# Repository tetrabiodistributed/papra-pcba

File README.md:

# PAPRA Printed Circuit Board Assembly (PCBA)

PAPRa PCBA - printed circuit board assembly for the PAPRa M12 Controller

Full documentation page for building the PAPRa can be found here: https://tetrabiodistributed.github.io/papra/

Firmware for flashing the PAPRA PCBA can be found here: https://github.com/tetrabiodistributed/papra-pcb-firmware/tree/main/papracode

## PAPRa PCBA comes in 2 form factors

### Thru Hole Technology

* Part Number A-TET-001113
* Suitable for hand soldering
* Larger form factor
* Easy to assemble, intended for novice 
* BOM parts should be easy to source
* Uses Adafruit QT PY or Seeed Xiao microcontroller board
* Firmware: TBD

### SMT

* Part Number A-TET-001100
* Suitable for mass production
* Smallest form factor
* Machine assembly recommended, very difficult to hand solder
* Lowest BOM cost
* Uses ATTINY 0/1/2-Series 14pin SOIC
* Firmware found here: https://github.com/tetrabiodistributed/papra-pcb-firmware/tree/main/papracode

## Notes for programming

* Make a UPDI Programmer: https://create.arduino.cc/projecthub/john-bradnam/create-your-own-updi-programmer-1e55f1?ref=user&ref_id=466812&offset=6
* The board features a UPDI header on the top left of the PCB (top being the side with the battery connectors) the pins are top to bottom 5V, GND and data. 
* Setup Arduino: https://www.hackster.io/john-bradnam/using-the-new-attiny-processors-with-arduino-ide-612185
* You will need to use the megaTinyCore library by SpenceKonde: https://github.com/SpenceKonde/megaTinyCore

Upload settings can be found in the arduino program. 

Please note that there are a number of ATTiny SKUs that are compatible with this PCB and code, please refer to the below table when choosing an appropriate IC.

| Model number   | Confirmed   | Notes                             |
| -------------- | ----------- | --------------------------------- |
| ATtiny204SSN_, | Yes         | See Below(1)  |
| ATtiny404SSN_, | Yes         |    	                           |
| ATtiny804SSN_, | Yes         |                                   |
| ATtiny1604SSN_,| Yes         |    	                           |
| ATtiny214SSN_, | Yes         | See Below(1)  |
| ATtiny414SSN_, | Yes         |    	                           |
| ATtiny814SSN_, | Yes         |                                   |
| ATtiny1614SSN_,| Yes         |    	                           |
| ATtiny1624SSU, | Yes         |    	                           |

(1)ATtiny 204 and 214 have limited (2K) flash memory for program space, but the firmware can be made to fit by sacraficing the bootup LED sequence.

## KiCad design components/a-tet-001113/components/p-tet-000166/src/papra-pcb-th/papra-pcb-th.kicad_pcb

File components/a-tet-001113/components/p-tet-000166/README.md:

# P-TET-000166 — PAPRa M12 Controller PCB (through-hole)

## Files

| Path | What |
|---|---|
| `src/Papra TH_eagle.sch`, `src/Papra TH_eagle.brd` | Original Eagle 9.6.2 design. Source of truth for the migration. |
| `src/papra-pcb-th/` | KiCad 10 project **generated** from the Eagle files by `make import`. Do not hand-edit until the Eagle files are retired; regenerate instead. |
| `src/papra-pcb-th/papra-pcb-th.pretty/`, `papra-pcb-th.kicad_sym` | Project footprint/symbol libraries extracted from the Eagle design. |
| `src/papra-pcb-th/3d/` | Manufacturer STEP models (see `3d/SOURCES.md`). |
| `dist/Papra TH_eagle_2023-03-08.zip` | Gerbers Eagle produced for the fab run. The Gerber check compares against these. |
| `../../lcsc-parts.csv` | LCSC numbers looked up for the BOM MPNs (`make lcsc`). |

## How the migration is validated (`make check`, from the repo root)

1. **Board structure** (`checks/test_board.py`): every Eagle element is a KiCad footprint with the
   same value, position, side; every pad has the same position, drill and copper size; every
   net has the same pads; the GND pour survived.
2. **Schematic** (`checks/test_schematic.py`): KiCad's own netlister reproduces Eagle's nets pad
   for pad; ERC has no errors; KiCad's schematic-parity DRC agrees board with schematic; the
   board passes the design rules translated from Eagle's `.brd`.
3. **Fab output** (`checks/test_gerbers.py`): Gerbers plotted from the KiCad board are rendered
   and XOR-compared per layer against the 2023 Eagle Gerbers; the drill files must list
   identical holes. Overlays land in `build/p-tet-000166/render/diff-<layer>.png`.
4. **3D placement** (`checks/test_models.py`): every model is placed with KiCad's own model
   transform (`checks/model_geom.py`, the matrix chain from the 3D viewer, on the geometry
   KiCad loads from the STEP file) and must sit on its side of the board with only its pins
   through it, landing on its pads. Manufacturer parts are held to datasheet numbers in
   `checks/parts.py` `PLACEMENT` (height, pin length, footprint, which way it faces).
5. **Determinism** (`checks/test_project.py`): a re-import of unchanged sources gives
   byte-identical files. kicad-cli and pcbnew mint random UUIDs and write elements in memory
   order; `checks/stable_ids.py` renames UUIDs by ordinal and sorts the board's blocks.

Known, accepted differences are listed in `checks/config.py` and `checks/project.py`.

## Regenerating

```
make import     # Eagle -> KiCad (board via kicad-cli, schematic via checks/sch_convert.py)
make check
make outputs    # ERC/DRC reports, PDFs, BOMs, Gerbers, drills, STEP, renders in build/
```

## Working in the KiCad GUI

- Open `src/papra-pcb-th/papra-pcb-th.kicad_pro`, not the `.kicad_sch` or `.kicad_pcb` on
  their own. The project carries the symbol/footprint library tables and the DRC/ERC
  severities; opened standalone, KiCad reports every library as missing and uses its
  default rules.
- Close KiCad before `make import`. KiCad keeps the project settings in memory and writes
  them back on save, which silently reverts the generated `.kicad_pro`.

## Additions over the Eagle design

- **Plated slots for the DC jack.** Eagle emulated the PJ-066A blade slots with pads, end
  holes and milling; the KiCad board has one plated oval pad per blade (`checks/parts.py`
  `SLOT_PADS`), which is what the fab produces and what DRC can reason about.
- **QR code on the bottom silkscreen** linking to https://tetrab.io, generated by
  `checks/qr.py` (content and module size in `checks/parts.py`) and placed automatically in
  the largest area free of holes, pads and other silkscreen. It is excluded from the Gerber
  comparison against the 2023 Eagle output, as are the slot pads.
- **3D models.** Standard parts use the models shipped with KiCad. The FASTON tabs, BNC,
  potentiometer and XIAO use manufacturer STEP files under `src/papra-pcb-th/3d/`
  (`3d/SOURCES.md`); their rotation and offset were solved, not eyeballed, by
  `checks/model_solve.py` from the model geometry and the datasheet rules, and are pinned in
  `checks/models.py`. The DC jack is drawn with KiCad's PJ-063AH model because Same Sky
  publishes none for the PJ-066A. To re-solve after changing a model or a rule:

  ```
  .venv/bin/python -m checks.model_solve POT1 H2 BATT+0 U1
  ```

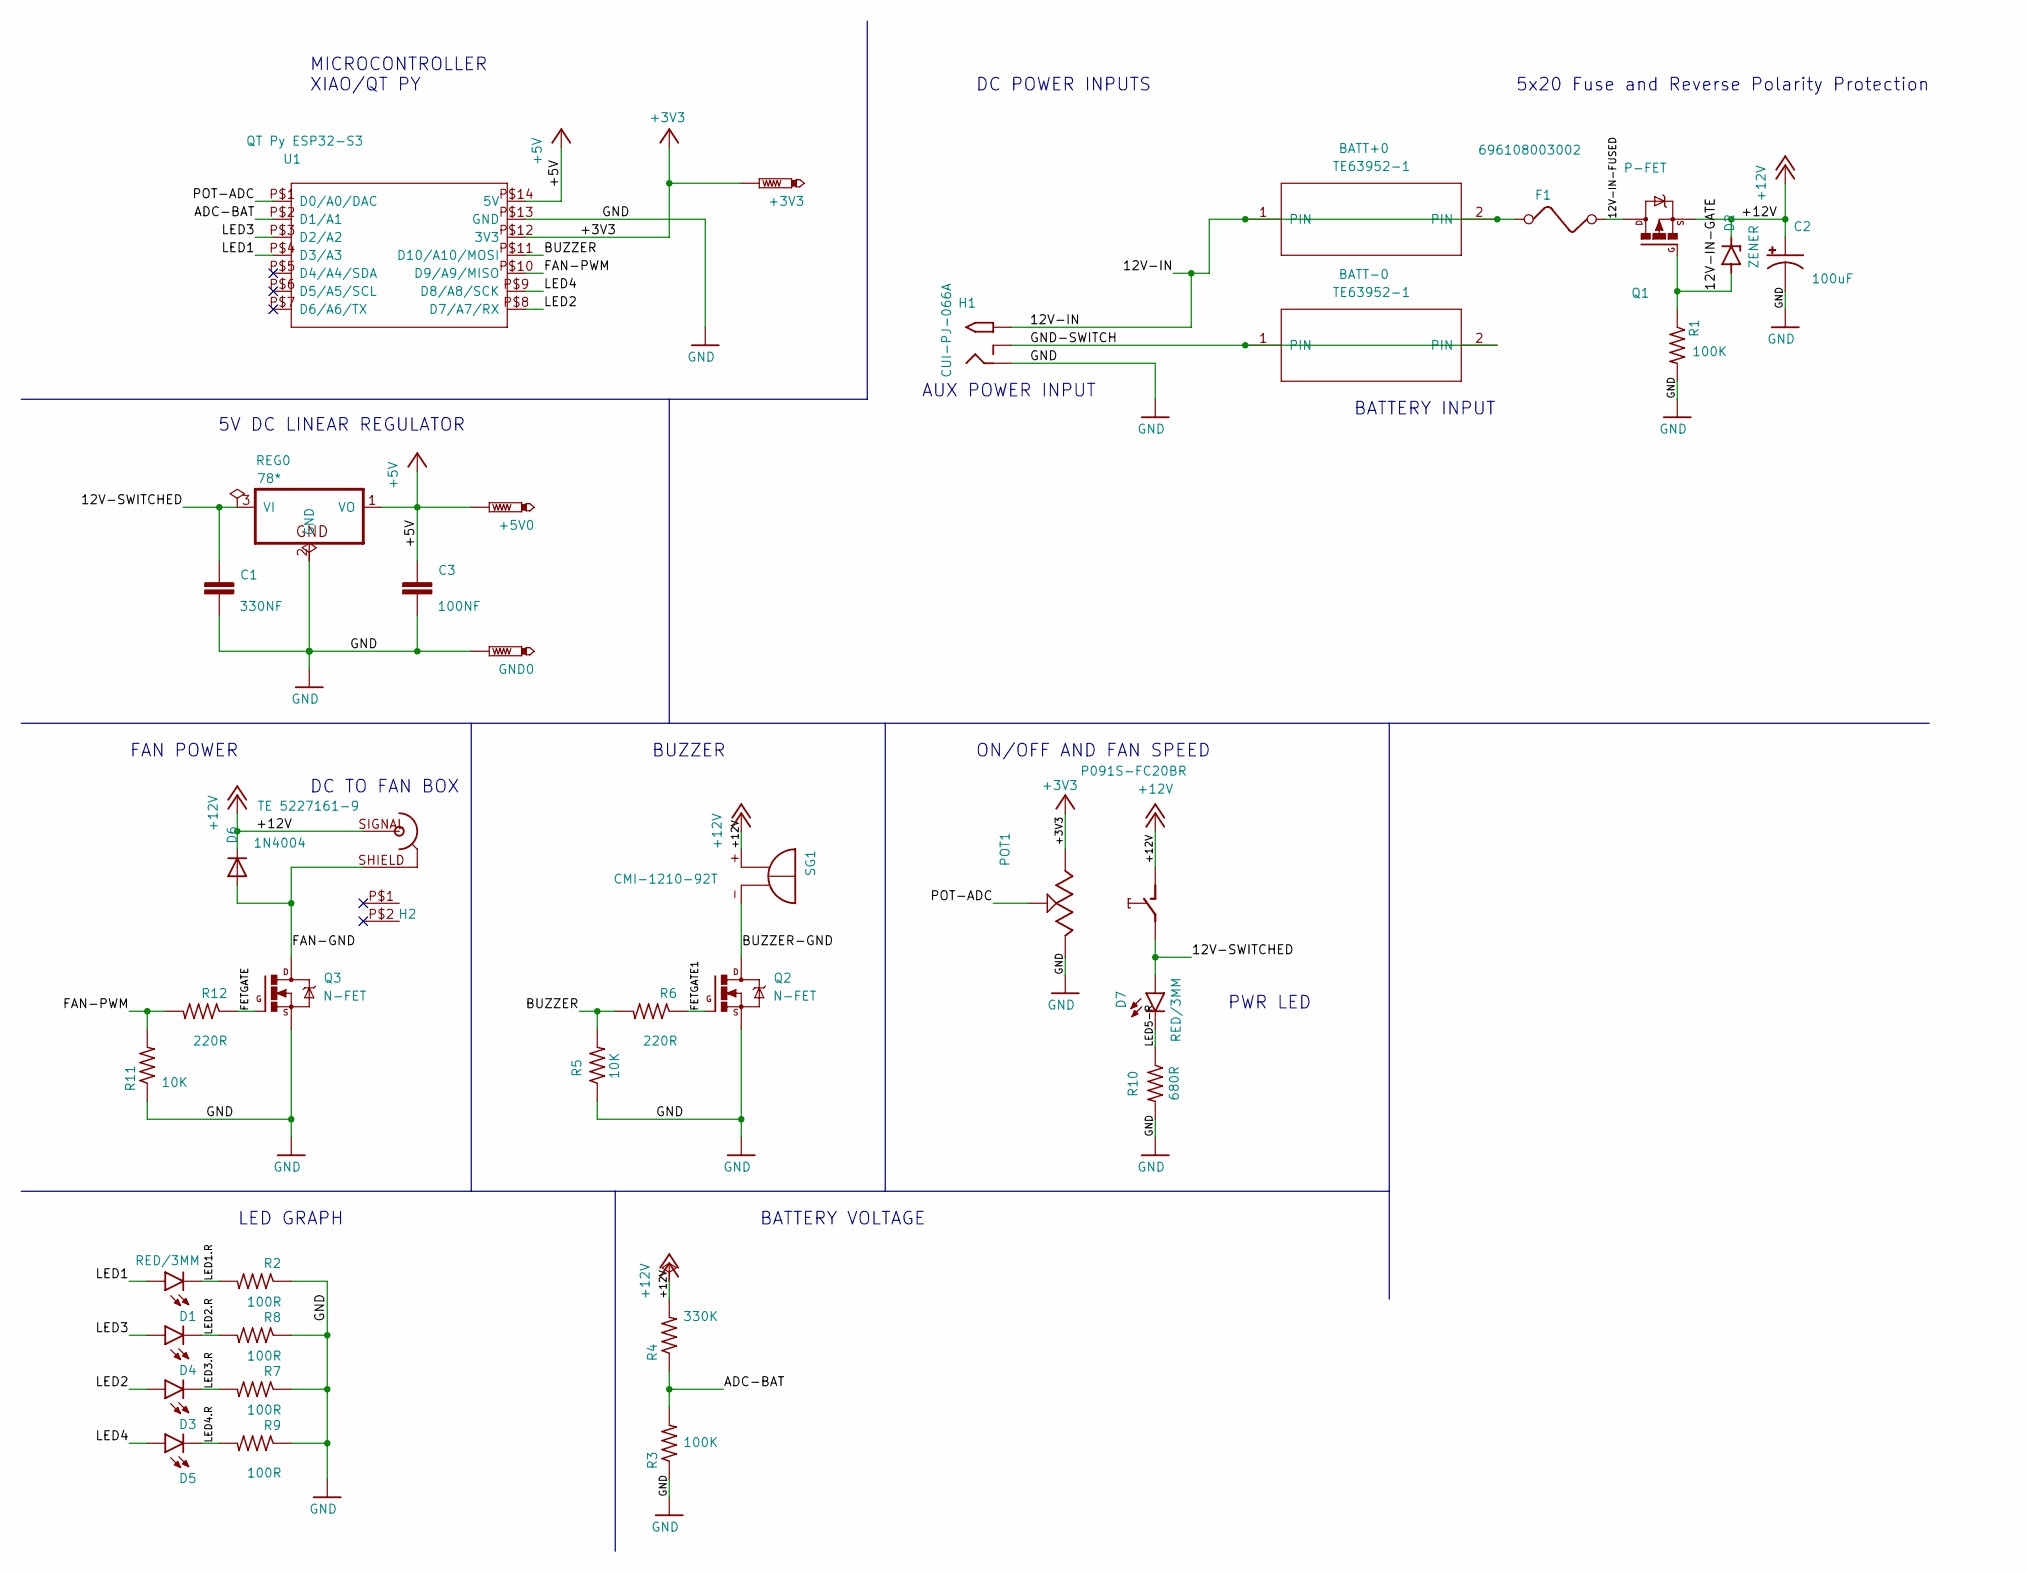
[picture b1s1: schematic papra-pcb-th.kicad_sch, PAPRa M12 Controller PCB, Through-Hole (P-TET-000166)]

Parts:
+3V3, +5V0: PTR1; P1-17
BATT+0: TE63952-1; MPN 63952-1; Digi-Key_PN A116309CT-ND
BATT-0: TE63952-1; MPN 63952-1; Digi-Key_PN A116309CT-ND
C1: 330NF; CAP-PTH-SMALL-KIT; MPN FG14X7R1H334KNT06; Digi-Key_PN 445-173139-1-ND
C2: 100uF; CPOL-RADIAL-2.5MM-6.5MM; MPN ESH227M016AE3AA; Digi-Key_PN 399-6566-ND
C3: 100NF; CAP-PTH-SMALL-KIT; MPN FG14X7R2A104KNT06; Digi-Key_PN 445-173141-1-ND
D1, D3, D4, D5, D7: RED/3MM; LED_3MM; MPN WP710A10SURCK; Digi-Key_PN 754-WP710A10SURCK-ND
D2: ZENER; DIODE-AXIAL; MPN 1N5240BTR; Digi-Key_PN 1N5240BFSCT-ND
D6: 1N4004; DO41-10; MPN 1N4004B-G; Digi-Key_PN 641-1999-ND
F1: 696108003002; FUSE; MPN 696108003002; Digi-Key_PN 732-11376-ND
GND0: PTR1; P1-17
H1: CUI-PJ-066A; DCJACK-PJ-066A-SLOT; MPN PJ-066A; Digi-Key_PN CP-066A-ND
H2: TE 5227161-9; TE-BNC; MPN 5227161-9; Digi-Key_PN A32261-ND
POT1: P091S-FC20BR; MPN P091S-FC20BR10K; Digi-Key_PN 987-1283-ND
Q1: P-FET; TO220BV; MPN G75P04FI; Digi-Key_PN 3141-G75P04FI-ND
Q2, Q3: N-FET; TO220BV; MPN IPP040N06NF2SAKMA1; Digi-Key_PN 448-IPP040N06NF2SAKMA1-ND
R1, R3: 100K; 0207_10; MPN MFR-25FRF52-100K; Digi-Key_PN 13-MFR-25FRF52-100KCT-ND
R2, R7, R8, R9: 100R; 0207_10; MPN MFR-25FRF52-100R; Digi-Key_PN 13-MFR-25FRF52-100RCT-ND
R4: 330K; 0207_10; MPN MFR-25FRF52-330K; Digi-Key_PN 13-MFR-25FRF52-330KCT-ND
R5, R11: 10K; 0207_10; MPN MFR-25FRF52-10K; Digi-Key_PN 13-MFR-25FRF52-10KCT-ND
R6, R12: 220R; 0207_10; MPN MFR-25FRF52-220R; Digi-Key_PN 13-MFR-25FRF52-220RCT-ND
R10: 680R; 0207_10; MPN MFR-25FRF52-680R; Digi-Key_PN 13-MFR-25FRF52-680RCT-ND
REG0: 78*; TO92; MPN UA78L05ACLPME3; Digi-Key_PN 296-50712-1-ND
SG1: CMI-1210-92T; F_TMB; MPN CMI-1210-92T; Digi-Key_PN CMI-1210-92TCMI-1210-92T
U1: QT Py ESP32-S3; MODULE14P-TH+PAD; MPN 5325; Digi-Key_PN 1528-5325-ND

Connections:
+3V3: +3V3.TP, POT1.3, U1.P$12 (3V3)
+5V: +5V0.TP, C3.1, REG0.1 (VO), U1.P$14 (5V)
+12V: C2.1 (+), D2.2 (C), D6.C, H2.SIGNAL (P1), POT1.COM (4), Q1.S, R4.2, SG1.+
/12V-IN: BATT+0.1, BATT+0.2, F1.1, H1.PWR (TIP)
/12V-IN-FUSED: F1.2, Q1.D
/12V-IN-GATE: D2.1 (A), Q1.G, R1.1
/12V-SWITCHED: C1.1, D7.A, POT1.NO (5), REG0.3 (VI)
/ADC-BAT: R3.2, R4.1, U1.P$2 (D1/A1)
/BUZZER: R5.2, R6.2, U1.P$11 (D10/A10/MOSI)
/BUZZER-GND: Q2.D, SG1.-
/FAN-GND: D6.A, H2.SHIELD (P2), Q3.D
/FAN-PWM: R11.2, R12.2, U1.P$10 (D9/A9/MISO)
/FETGATE: Q3.G, R12.1
/FETGATE1: Q2.G, R6.1
/GND-SWITCH: BATT-0.1, BATT-0.2, H1.GNDBREAK (RING_SW)
/LED1: D1.A, U1.P$4 (D3/A3)
/LED1.R: D1.K (C), R2.2
/LED2: D3.A, U1.P$8 (D7/A7/RX)
/LED2.R: D4.K (C), R8.2
/LED3: D4.A, U1.P$3 (D2/A2)
/LED3.R: D3.K (C), R7.2
/LED4: D5.A, U1.P$9 (D8/A8/SCK)
/LED4.R: D5.K (C), R9.2
/LED5-R: D7.K (C), R10.1
/POT-ADC: POT1.2, U1.P$1 (D0/A0/DAC)
GND: C1.2, C2.2 (-), C3.2, GND0.TP, H1.GND (RING), POT1.1, Q2.S, Q3.S, R1.2, R2.1, R3.1, R5.1, R7.1, R8.1, R9.1, R10.2, R11.1, REG0.2 (GND), U1.P$13 (GND)

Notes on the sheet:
FAN POWER
AUX POWER INPUT
LED GRAPH
BUZZER
5x20 Fuse and Reverse Polarity Protection
5V DC LINEAR REGULATOR
ON/OFF AND FAN SPEED
BATTERY VOLTAGE
PWR LED
DC TO FAN BOX
MICROCONTROLLER XIAO/QT PY
DC POWER INPUTS
BATTERY INPUT

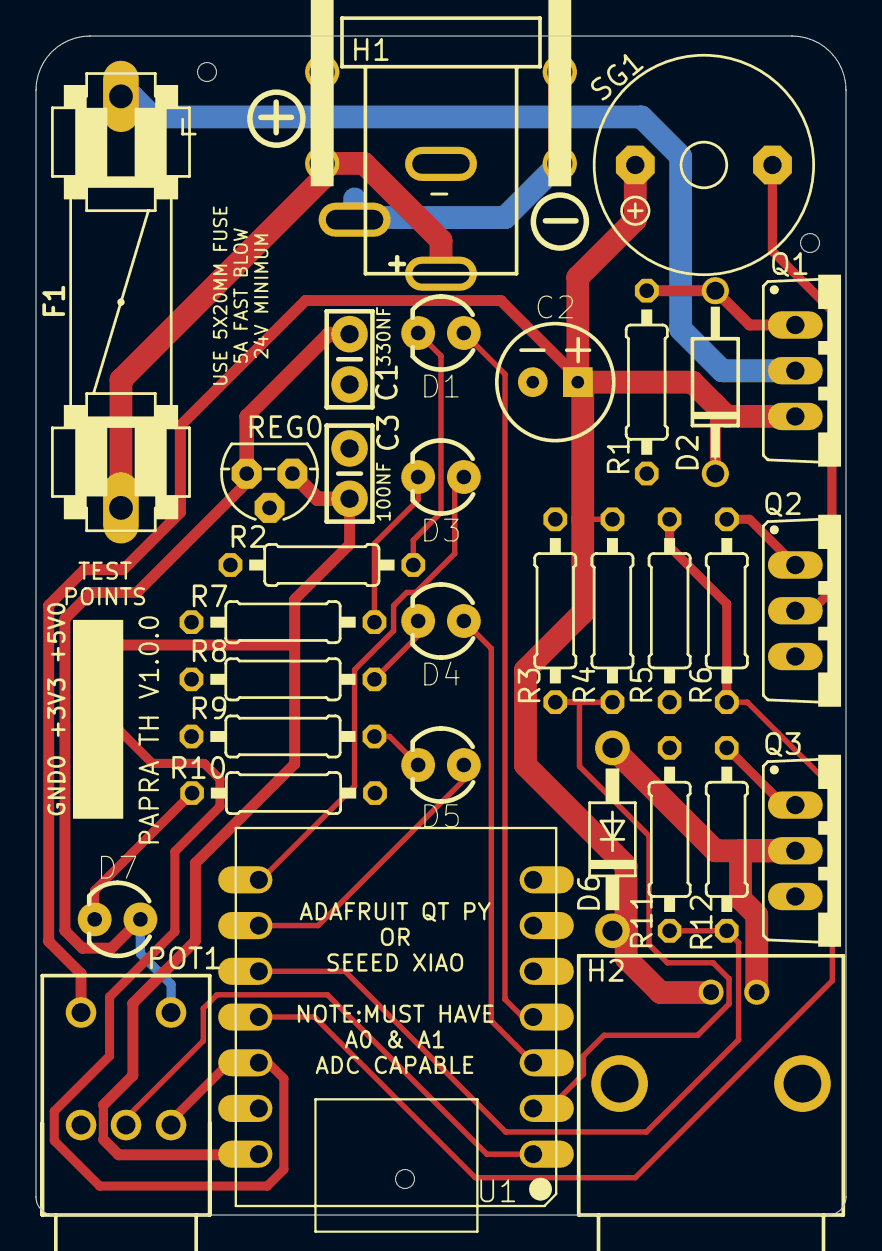
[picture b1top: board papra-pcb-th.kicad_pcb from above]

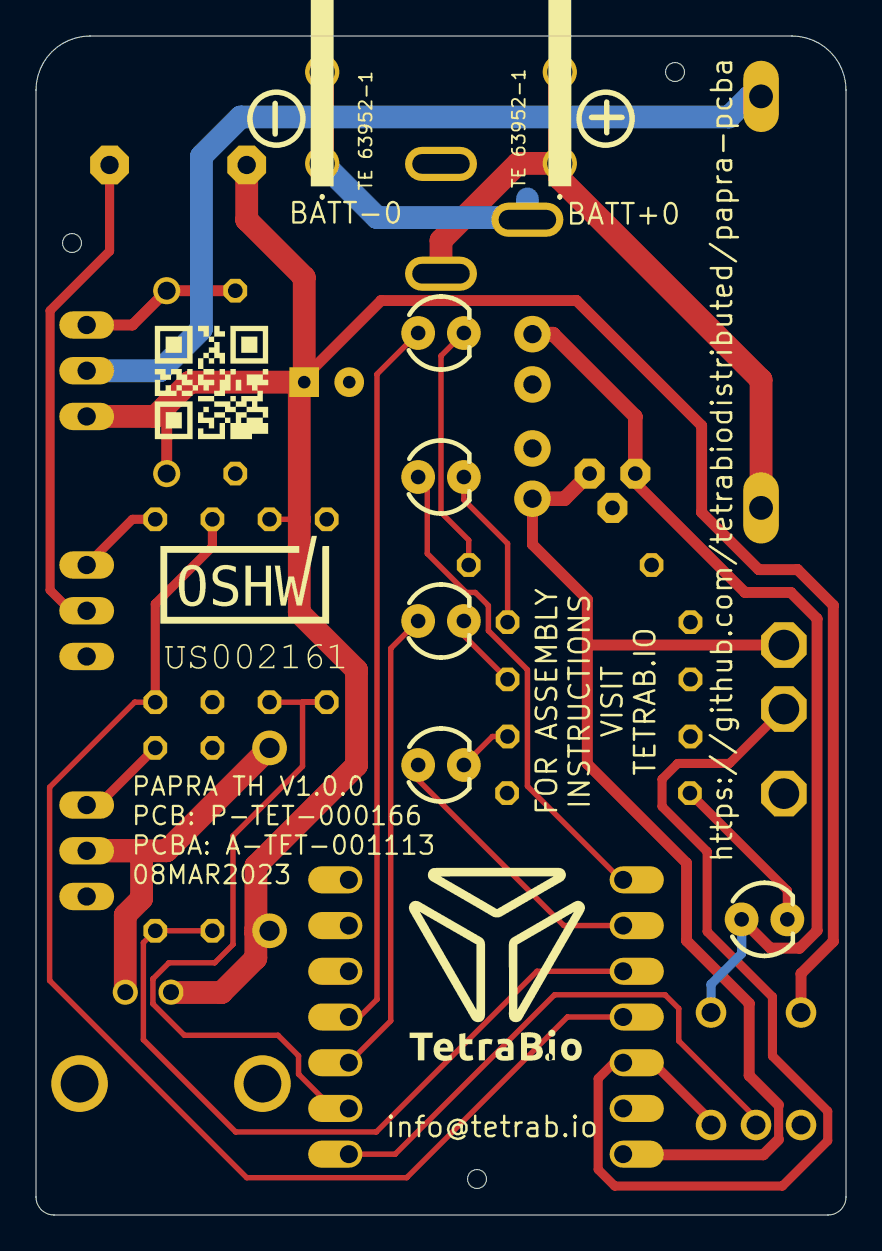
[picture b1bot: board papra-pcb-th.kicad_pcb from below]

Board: 2 copper layers, 45.0 x 65.5 mm, 40 parts (2 on the bottom side), 26 nets.

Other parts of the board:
UNK_HOLE_0: dummyfp0
UNK_HOLE_1: dummyfp1
UNK_HOLE_2: dummyfp2

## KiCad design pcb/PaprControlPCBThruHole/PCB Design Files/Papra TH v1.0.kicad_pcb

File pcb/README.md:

The Tetra PAPRA project requires 1 PCBA, v.7 or newer.

PaprControlPCB - this is a speed controller that allows for adjusting speed of blower

Note:
A PCB is a bare board.
A PCBA is an assembly of a PCB and OTS (off the shelf) components, which are typically a mix of surface mount and thru-hole components.

PCBA Bring-Up Instructions:

1. Connect power to the board via 2.5mm DC jack (H1) using 12V Nominal (7V min, 14V max) DC power, ideally current limitable. Do not connect fan to the output connector at this time.

* Note DC polarity on connector is important, center pin is positive.
   * Insertion length on connector is 8.4mm, so body of mating jack should be at least this length.
   * For use with a bench power supply, a cut-end cable option is [Tensility CA-2185](https://www.digikey.com/en/products/detail/tensility-international-corp/CA-2185/568576) 
   * For a standalone power adapter, consider a [Tri-Mag L6R06H-120 12V/6W supply](https://www.digikey.com/en/products/detail/tri-mag-llc/L6R06H-120/7682617)
2. For adjustable power supply, set the voltage to12V and set initial current limit to ~25mA, which should be sufficient to power up processor and drive LEDs.
3. Turn the potentiometer/switch (POT1) to ON. 

4. Confirm the power LED (LED5) illuminates with 12V power.

5. Measure 5V regulator (U1) is outputting 5VDC. This can be inspected with a voltmeter measuring the UDPI header as follows:
   * Pin 2 is GND
   * Pin 3 is +5V
6. At this point, the board is powered and ready for programming via UPDI. Follow the instructions [here.](https://github.com/tetrabiodistributed/PAPRA-PCB/blob/main/README.md).
7. Upon successful completion of firmware installation, confirm the board powers up and the 4 LEDs (LED1 - LED4) light up at boot up in a sequence.
8. For boards with the buzzer installed, confirm the buzzer chirps at bootup.
9. In preparation for testing with a DC blower and battery, disconnect the DC jack from H1.
10. Source a fully charged [Milwaukee M12 Red Lithium Battery 48-11-2401](https://www.milwaukeetool.com/Products/Batteries-and-Chargers/M12-Batteries-and-Chargers/48-11-2401) or similar. 
11. Connect DC power to BNC connector (H2).
* WARNING: If the board is not installed in the battery housing, pay careful attention to the polarity
12. Turn on potentiometer (POT1) and adjust the fan speed from high to low, which checking the DC blower is working and speed is changing with potentiometer adjustments.

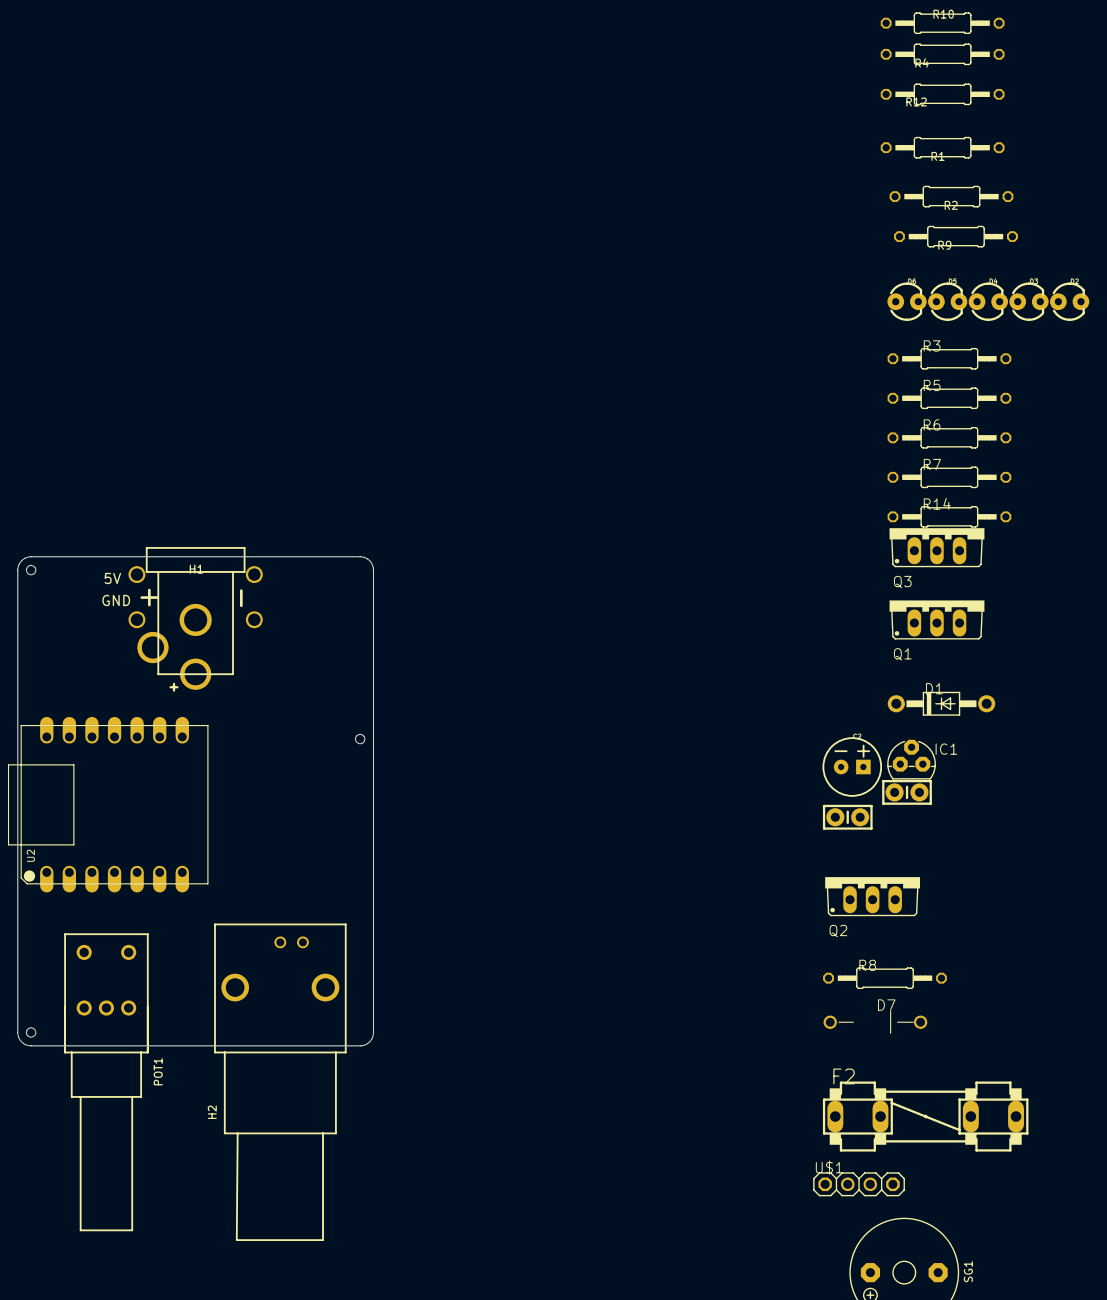
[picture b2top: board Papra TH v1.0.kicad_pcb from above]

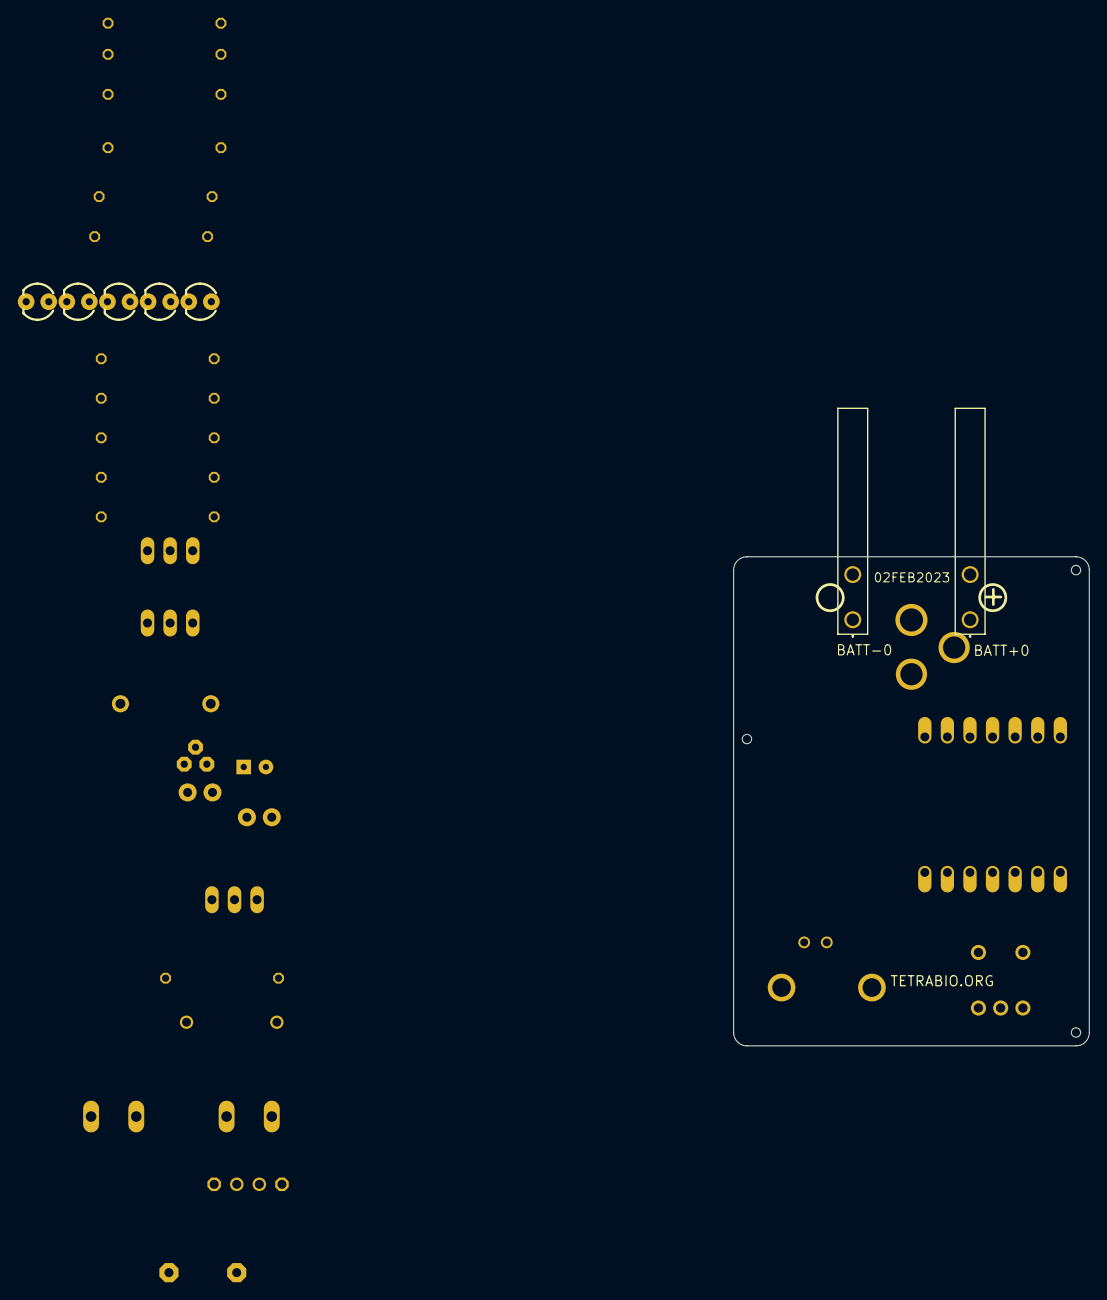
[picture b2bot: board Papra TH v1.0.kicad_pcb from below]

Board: 2 copper layers, 40.0 x 55.0 mm, 38 parts (2 on the bottom side), 28 nets, no tracks yet.

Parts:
@HOLE0, @HOLE1, @HOLE2: (no value)
BATT+0: TE63952-1
BATT-0: TE63952-1
C1: 0.1uF; CAP-PTH-SMALL-KIT
C2: 100uF; CPOL-RADIAL-2.5MM-6.5MM
C3: 0.33uF; CAP-PTH-SMALL-KIT
D1: 1N4004; DO41-10
D2: BLUE/3MM; LED_3MM
D3, D4, D5, D6: RED/3MM; LED_3MM
D7: 1N5240B; DIODE-AXIAL
F2: KEYSTONE 4628; FH_5X20
H1: M-CUI-PJ-066A; DCJACK-PJ-066A
H2: TE-BNC
IC1: 78L05Z; TO92
POT1: P091S-FC20BR
Q1, Q3: NMOSFET; TO220BV
Q2: FQP27P06; TO220BV
R1, R9, R12: 10K; 0207_12
R2: 18K; 0207_12
R3, R4, R5, R6, R7, R14: 120R; 0207_12
R8: 100K; 0207_12
R10: 1K2; 0207_12
SG1: YS-MBZ12095DYB12 C409840; F_TMB
U2: QT Py ESP32-S3; MODULE14P-TH+PAD
U$1: 4X1; 01X4

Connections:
12V-IN: BATT+0.1, BATT+0.2, F2.1A, F2.1B, H1.PWR
12V-IN-FUSED: F2.2A, F2.2B, Q2.D
12V-IN-GATE: D7.1, Q2.G, R8.1
12V-SWITCHED: C3.1, D2.A, IC1.3, POT1.COM
+3V3: POT1.3, U2.P$12, U$1.3
+5V: C1.1, IC1.1, U2.P$14
+12V: C2.1, D1.C, D7.2, H2.SIGNAL, POT1.NO, Q2.S, R2.2, SG1.+
ADC-BAT: R1.2, R2.1, U2.P$2
BUZZER: R12.2, R14.2, U2.P$11
BUZZER-GND: Q1.D, SG1.-
FAN-GND: D1.A, H2.SHIELD, Q3.D
FAN-PWM: R7.2, R9.2, U2.P$10
FETGATE: Q3.G, R7.1
FETGATE1: Q1.G, R14.1
GND: C1.2, C2.2, C3.2, H1.GND, IC1.2, POT1.1, Q1.S, Q3.S, R1.1, R3.1, R4.1, R5.1, R6.1, R8.2, R9.1, R10.2, R12.1, U2.P$13, U$1.4
GND-SWITCH: BATT-0.1, BATT-0.2, H1.GNDBREAK
LED1: D3.A, U2.P$3
LED2: D4.A, U2.P$4
LED3: D5.A, U2.P$8
LED4: D6.A, U2.P$9
LED5-R: D2.K, R10.1
unnamed: D4.K, R3.2
unnamed: D3.K, R4.2
unnamed: D5.K, R5.2
unnamed: D6.K, R6.2
POT-ADC: POT1.2, U2.P$1
SCL: U2.P$6, U$1.2
SDA: U2.P$5, U$1.1

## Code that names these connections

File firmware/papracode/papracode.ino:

/*
  papracode
    - Reads battery voltage and lights up LEDs to mimic M12 battery fuel gauge
    - Reads user pot to control PWM of fan

  PCB is compatible with all 0/1/2-Series 14 pin ATtiny chips
  For chips with 2K flash (ATtiny204 & ATtiny404), the Preprocessor directive must be uncommented
*/
//#define TWOKFLASHCHIP //uncomment line when programming ATtiny204 or ATtiny214
  
// Compile with Arduino 1.8.13 or later.
// Install MegaTinyCore via the Boards Manager
// MegaTinyCore 2.3.2
// Note:bootloader not used, so many options below will not be relevent
//  Board: ATtiny 3224/1624/1614/1604/814/804/424/414/404/214/204
//  Chip or Board: Select your chip
//  Clock: 20MHz internal
//  millis()/micros() TCB0 (breaks tone() and Servo)
//  Startup Time: 8ms
//  BOD Voltage level: Any, BOD not used without bootloader
//  BOD Mode when Active/Sleeping: Any, BOD not used without bootloader
//  Save EEPROM: Any, not used without bootloader
//  UPDI/Reset Pin Function: Any, not used without bootloader 
//  Voltage Baud Correction: Closer to 5V

#ifdef MILLIS_USE_TIMERA0
#error "This sketch takes over TCA0 - please use a different timer for millis"
#endif

#ifndef MILLIS_USE_TIMERB0
#error "This sketch is written for use with TCB0 as the millis timing source"
#endif

// Pin connections per PAPR V0.5 PCB
// PA0 - UPDI/RESET
// PA1 - ADC - BATTERY
// PA2 - ADC = POTENTIOMETER
// PA3 - UNUSED
// PA4 - LED4 
// PA5 - LED1
// PA6 - LED2
// PA7 - LED3
// PB0 - PWM - FAN (uses Timer TCA0)
// PB1 - BUZZER
// PB2 - UART TX
// PB3 - UART RX

int analogBatt  = PIN_A1;  // AIN1 - 10 bit resolution on ADC 
int analogPot   = PIN_A2;  // AIN2 - Fan speed control POT with on/off switch
//int UNUSED    = PIN_PA3; //v0.5 change
int led4        = PIN_PA4; //v0.5 change
int led1        = PIN_PA5;
int led2        = PIN_PA6;
int led3        = PIN_PA7;
int PWMPin      = PIN_PB0; // W00 8 bit resolution with Arduino AnalogWrite (v0.3 change)
int buzzerPin   = PIN_PB1; //v0.5 change

// Battery Voltage to Fuel Gauge
// > 4.12V/Cell = 100% - 78% Battery  = 4 LEDs         => 899 > adc > 864
// > 3.95V/Cell =  77% - 55% Battery  = 3 LEDs         => 864 > adc > 816
// > 3.70V/Cell =  54% - 33% Battery  = 2 LEDs         => 816 > adc > 781
// > 3.54V/Cell =  32% - 10% Battery  = 1 LEDs         => 781 > adc > 712
// > 3.25V/Cell =  10% - 0%  Battery  = LEDS FLASHING  => 712 > adc > 618
// > 2.80V/Cell =  0%        Battery  = Shut Down

const int battADCMax  =  1023;
const int battADCFull =   899;
const int battADC78p  =   864;
const int battADC55p  =   816;
const int battADC33p  =   781;
const int battADC10p  =   712;
const int battADC0p   =   618;
const int battADCMin  =     0;


//Limits the min pot value     Voltage   Min PWM Percentage
const int minPWMfull =  50;  //11.85V      69     >77%
const int minPWM75p  =  55;  //11.10V      72     >54%
const int minPWM50p  =  61;  //10.62V      77     >33%
const int minPWM25p  =  70;  //9.75V       88     >10%
const int minPWM10p  = 126;  //8.40V      110     >0%
//These values were determined emperically by adjusting the input voltage and dialing the PWM down until motor stall

//State Machine states
const int batteryCheck = 7;
const int batteryFull  = 6;
const int battery75p   = 5;
const int battery50p   = 4;
const int battery25p   = 3;
const int battery10p   = 2;
const int batteryDead  = 1;

int batteryState = batteryCheck;

int offTime = 5; //ms
int onTime = 95;   //ms
int loopDelay = 25; //ms
int blinkCounter = 0;
const uint32_t numBatterySamples = 10;
uint32_t battery = 1023;
const uint32_t maxPot = 1023;
const uint32_t minPot = 0;
uint32_t fanPWM = 0;
uint32_t minPWM = minPWM10p;
uint32_t maxPWM = 255;
uint32_t rawADC = 0;

const int LEDFlashLoop  = 25; //decrease for 10% battery LED to blink faster

// the setup routine runs once when you press reset:
void setup() {
  // initialize the digital pin as an output.
  pinMode(led1, OUTPUT);
  pinMode(led2, OUTPUT);
  pinMode(led3, OUTPUT);
  pinMode(led4, OUTPUT);
  pinMode(buzzerPin, OUTPUT);
  pinMode(PWMPin, OUTPUT);  //PB0 - TCA0 WO0, pin9 on 14-pin parts
  //See http://ww1.microchip.com/downloads/en/Appnotes/TB3217-Getting-Started-with-TCA-DS90003217.pdf
  TCA0.SINGLE.CTRLB = ( TCA_SINGLE_CMP2EN_bm  | TCA_SINGLE_WGMODE_SINGLESLOPE_gc ); //Single PWM on WO0 singleslope
  TCA0.SINGLE.PER   = 0xFF; // Count down from 255 on WO0/WO1/WO2
  TCA0.SINGLE.CTRLA = ( TCA_SINGLE_CLKSEL_DIV4_gc | TCA_SINGLE_ENABLE_bm ); //enable the timer with prescaler of 4

  digitalWrite(led1, HIGH);
  digitalWrite(led2, HIGH);
  digitalWrite(led3, HIGH);
  digitalWrite(led4, HIGH);
  digitalWrite(buzzerPin,LOW);
  digitalWrite(PWMPin, maxPWM); //Turn on fan 100%
#ifdef TWOKFLASHCHIP
  delay(1000);
#else 
  Serial.begin(115200);
  Serial.println("Starting up");
  Serial.println("PAPRA 15MAY2021");
  Serial.println("PCB v0.5");
  Serial.println("AtTiny 0/1/2-Series 14 pin");
  Serial.println("Tetra Bio Distributed 2021");
  for (int i = 0; i <= 4; i++) { //startup knightrider 
    digitalWrite(led1, LOW);  delay(onTime);
    digitalWrite(led1, HIGH); 
    digitalWrite(led2, LOW);  delay(onTime);
    digitalWrite(led2, HIGH); 
    digitalWrite(led3, LOW);  delay(onTime);
    digitalWrite(led3, HIGH); 
    digitalWrite(led4, LOW);  delay(onTime); delay(onTime);
    digitalWrite(led4, HIGH); 
    digitalWrite(led3, LOW);  delay(onTime);
    digitalWrite(led3, HIGH); 
    digitalWrite(led2, LOW);  delay(onTime);
    digitalWrite(led2, HIGH); 
    digitalWrite(led1, LOW);  delay(onTime);
    digitalWrite(led1, HIGH); delay(offTime);
  }
#endif
}

// the loop routine runs over and over again forever:
void loop() {
  delay(25);
  //Clamp and rescale potentiometer input from a 10bit value to 8 bit
  if (maxPWM > 0) {
    rawADC = analogRead(analogPot);
    fanPWM = map( rawADC, minPot, maxPot, minPWM, maxPWM ); //scale knob, 10 bits to 8 bits (v0.3 change)
  } 
  else {
    fanPWM = maxPWM;
  }  
  analogWrite(PWMPin, fanPWM);
  battery = battery = ( ( battery * ( numBatterySamples - 1 ) ) + analogRead(analogBatt) ) / numBatterySamples;
  switch (battery) {
    case battADC78p ... battADCMax: // Full = 78% - 100%
      if (batteryState > batteryFull) {
        batteryState = batteryFull;
        digitalWrite(led1, LOW);  //All LEDs ON
        digitalWrite(led2, LOW);
        digitalWrite(led3, LOW);
        digitalWrite(led4, LOW);
        minPWM = minPWMfull;
      }
      break;
    case battADC55p ... ( battADC78p - 1 ): // 75% = 55% - 77%
      if (batteryState > battery75p) {
        batteryState = battery75p;
        digitalWrite(led1, LOW);  //3 LEDs ON
        digitalWrite(led2, LOW);
        digitalWrite(led3, LOW);
        digitalWrite(led4, HIGH);
        minPWM = minPWM75p;
      }
      break;
    case battADC33p ... ( battADC55p - 1 ): // 50% = 33% - 54%
      if (batteryState > battery50p) {
        batteryState = battery50p;
        digitalWrite(led1, LOW);  //2 LEDs ON
        digitalWrite(led2, LOW);
        digitalWrite(led3, HIGH);
        digitalWrite(led4, HIGH);
        minPWM = minPWM50p;
      }
      break;
    case battADC10p ... ( battADC33p -1 ): // 25% = 10% - 32%
      if (batteryState > battery25p) {
        batteryState = battery25p;
        digitalWrite(led1, LOW);  //1 LED on
        digitalWrite(led2, HIGH);
        digitalWrite(led3, HIGH);
        digitalWrite(led4, HIGH);
        minPWM = minPWM25p;
      }
      break;
    case battADC0p ... ( battADC10p - 1) : // 10% - Need to blink LED
      if (batteryState > battery10p) {
        batteryState = battery10p;
        digitalWrite(led2, HIGH); //1 LED blinking
        digitalWrite(led3, HIGH);
        digitalWrite(led4, HIGH);
        digitalWrite(led1, LOW);
        digitalWrite(buzzerPin, HIGH);
        minPWM = minPWM10p;
      }
      break;
    case battADCMin ... (battADC0p - 1 ): // Shutdown
      if (batteryState > batteryDead) {
        batteryState = batteryDead;
        digitalWrite(led1, HIGH); //All LEDs off
        digitalWrite(led2, HIGH);
        digitalWrite(led3, HIGH);
        digitalWrite(led4, HIGH);
        maxPWM = 0; // turn off fan - overrides the measuremnt from above
      }
      break;
  }
  // For battery state of 0-10%, need to blink LED1 to indicate almost dead battery
  if (batteryState == battery10p){
    if (blinkCounter++ > LEDFlashLoop) {
      digitalWrite(led1, !digitalRead(led1));
      blinkCounter = 0;
    }
  }  
#ifdef TWOKFLASHCHIP

#else
  Serial.print(" Battery = ");       Serial.print(battery);
  Serial.print(" rawADC = ");        Serial.print(rawADC);
  Serial.print(" pwm = ");           Serial.print(fanPWM);
  Serial.print(" Battery State = "); Serial.println(batteryState);
#endif
}

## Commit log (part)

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2020-11-20 Adding notes to readme
2020-11-20 readme
2020-11-24 Added fuel gauge LED code
2020-11-25 Added state machine for LEDs
2020-11-26 Implemented in PWM to prevent motor stalling at low end
2020-11-28 Added battery smoothing, fixed scaling formula. Tested
2020-12-11 PCB v0.2
2020-12-11 Adding pdf schematic
2020-12-20 adding newer setup image - Correcting Clock setting to 20 MHz
    was 16 MHz
2021-01-09 v0.2 PCB updates and knob speed reverse
2021-01-10 Switching to AtTiny1604 for codespace headroom
2021-01-11 Papra PCB Ready for release
2021-01-15 Updating the boards for the 3rd build
2021-01-19 Updates/Fixes to PCB and PCBA files.
    Added TETRA logo to bottom silk
2021-01-19 design files
2021-01-21 Added 1A resettable fuse to 12V power
2021-01-22 Added CERN 2.0 P License
2021-01-28 20kHz PWM freq (need to test)
2021-02-01 20kHz PWM with re-calibrated minimum PWM value
2021-02-05 v0.3 release candidate
2021-02-06 Reverting back to v0.2
2021-02-07 v0.3 pcb
2021-02-08 DRU update to latest
2021-02-15 Updated fan box PCB to v0.3 (IP68 DC Jack)
2021-02-22 STEP file update
2021-02-22 Adding in drawings for the PCBA
2021-02-26 fixing pin# mistake in code comments
2021-02-26 Update README.md
    Update README.md with compatability table for ATTiny SKUs.
2021-02-28 Updated SerialEvent note for memory constrained ICs
2021-02-28 Update README.md
    Adding comments for the pinout of the UPDI header.
2021-03-01 adding engineering drawings
2021-03-03 Updating drawings per Darragh, command line gitignore
2021-03-05 Update drawings for March 2021 release
2021-03-10 Update README.md
    Update with new arduino config
2021-03-24 v.4 board files, released batch of 3 to OSH
2021-03-28 adding .hex
2021-04-17 Chip confirmation update
2021-04-24 PAPRA Control PCB v0.4 design and manufacturing
    3 Boards have been made (Oshpark), just pushing the documentation as v0.5 is imminent.
    Consider v0.4 a test version
2021-04-24 Remove fan box board files and update firmware
    Fan box no longer has PCB
    Firmware needs to run for v.3 or later
2021-04-24 Adding schematic for review
2021-04-26 V.5 with PCB layout, for review
2021-04-26 Moved Buzzer to W01 & LED4 to PA4
2021-04-26 Releasing to OSH
    - Fixed for JLC DRU
    - Unused pin tied to via & labeled PA3
    - Adding 2 vias to allow shorting the UPDI resistor for use with programmers that have the UPDI in-circuit
    - Tied the posts on the BNC together (can't tie to ground as we are switching ground)
    - Silkscreen touchups
2021-05-09 v.5 pcb code
2021-05-13 Eagle DRU
2021-05-13 firmware for v0.3 PCB
2021-05-13 Update chip list
2021-05-13 Update README.md
    Removed image that is being deleted and added info on where upload settings can be found.
2021-05-13 Updating readme
    Added note about commenting out the LED startup sequence to fit in a 2K flash code space
2021-05-13 update note on ATtiny204SSN_
2021-05-15 Firmware in Submodule
2021-05-16 Updating PCBA Drawing
2021-05-22 File cleanup
    Adding in JLC production files, updated BOMs and resolved conflict
2021-05-22 Documentation updates
    -PDFs for board assembly & M12 controller assembly
    -Adding firmware to right location
    -PCB Step cad model
2021-05-24 V.5 Release candidate
2021-05-24 Readme Update
2021-05-24 Firmware moved to submodule
2021-05-24 adding firmware location in readme
2021-05-24 Drawing update
2021-05-31 Rotate drawing
2021-05-31 Rotate Drawing
    Should be right this time
2021-05-31 Title block update
2021-05-31 Title block & partlist update
2021-07-27 Board ready for review
    Closes #53
2021-07-28 Updates based on feedback
2021-09-06 Adding gerbers
2022-05-16 Updating to v0.7
    Closes #59
2022-05-27 Updated changelogs for schematic & PCB
2022-12-17 Rename README to README.md
2022-12-17 Update README.md
    Formatting
2023-01-31 Adding images and grammar cleanup/spelling
2023-01-31 Adding punctuation
2023-02-02 DFM Update
    Closes #72
    Closes #73
    Closes #74
2023-02-16 Adding thru hole schematic design
2023-02-25 Adding KiCad Schematic
2023-02-25 Adding the PCB file for mechanical
    Sized at 40mm wide, symmetric. Added 10mm to length
2023-02-26 rescaffold file structure as DOF-component
    as to be able to accommodate both surface mount and through hole assembly options
2023-02-26 delete pcb/README.md
    as it's been replaced by assemblySteps.yaml in a-tet-001100
2023-02-26 rename kicad files to be dash-separated-lowercase
2023-02-26 add kicad project file for papra-pcb-th
2023-02-26 move Papra TH Schematic PDF to dist/
2023-02-26 update kicad project file for papra-pcb-th
    as to be able to open pcb and schematic in kicad
2023-02-26 Adding eagle footprints
2023-02-26 The whole folder
2023-02-26 attempting to resolve footprints
2023-03-03 update project name to papra-pcba
2023-03-03 move D-TET-001100-2 PDF to its dist/ directory
2023-03-08 Adding eagle design files, BOM and updating readme
2023-03-08 Ready for production - adding gerbers and final PCB design files
2023-03-13 Updated BOM
2023-04-30 correction on 10k
2023-04-30 Cleanup on resistors
    Changed to 1% tolerance
    Adding resistor manufacturer, manufacturer part number and description
2024-04-06 update README with link to papra documentaiton page
2025-03-29 remove out-of-date kicad files
2025-03-29 add updated kicad files for thruhole board imported from eagle
